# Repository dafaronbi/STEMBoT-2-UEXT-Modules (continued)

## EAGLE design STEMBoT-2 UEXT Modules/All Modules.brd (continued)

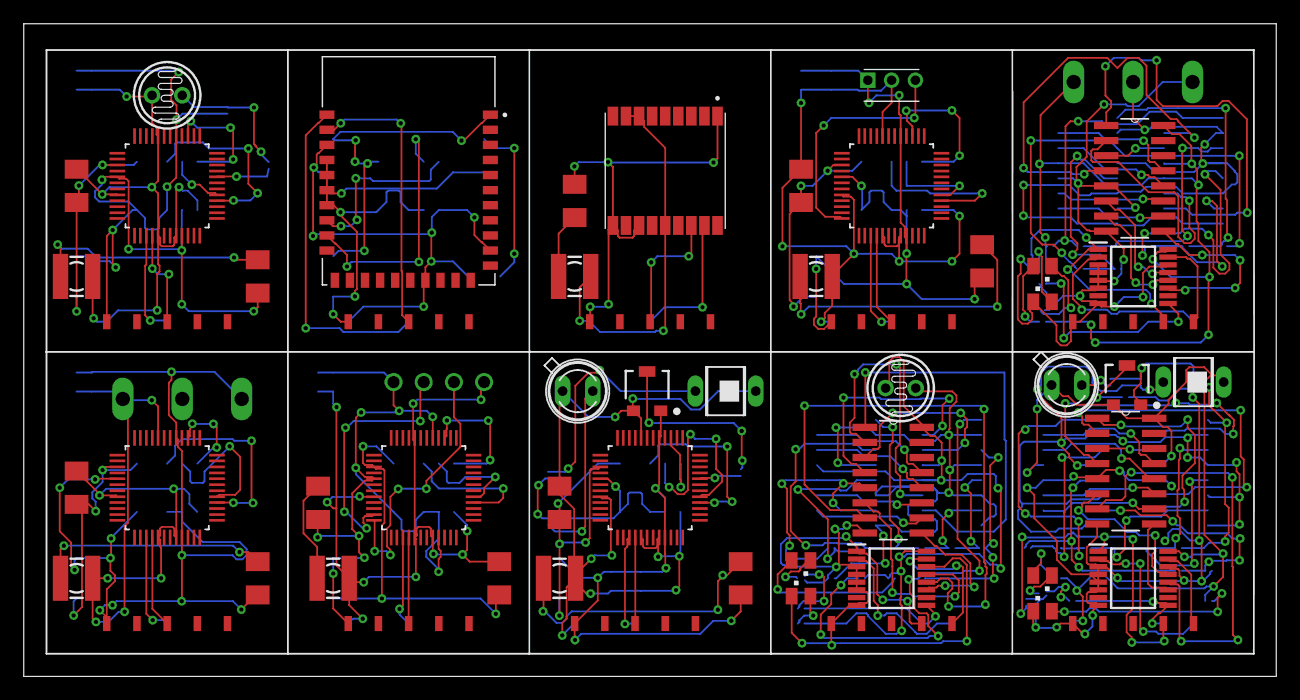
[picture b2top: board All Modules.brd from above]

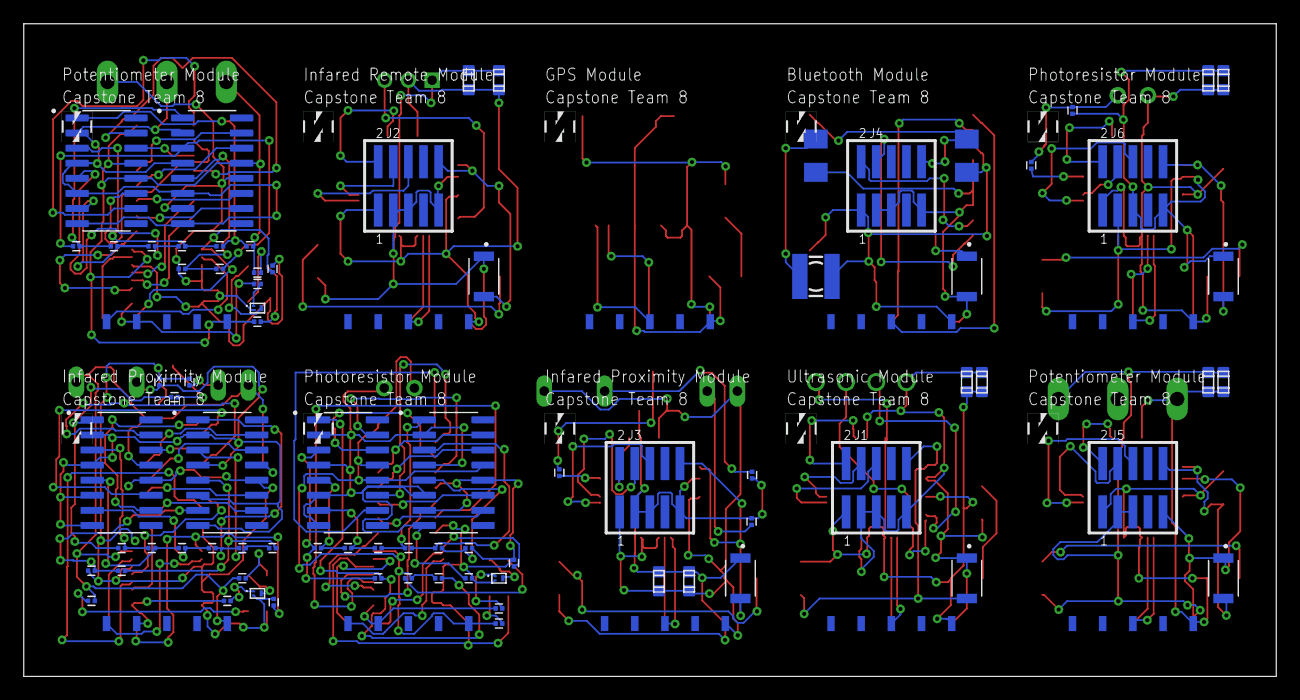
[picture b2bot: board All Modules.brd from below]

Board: 2 copper layers, 105.4 x 54.9 mm, 134 parts (79 on the bottom side), 157 nets.

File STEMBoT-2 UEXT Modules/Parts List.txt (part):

Partlist

Exported from All Modules.sch at 3/26/2020 1:25 PM

EAGLE Version 9.5.1 Copyright (c) 1988-2019 Autodesk, Inc.

Assembly variant: 

Part     Value                Device               Package               Library               Sheet

C1       CAPACITORS-0603      CAPACITORS-0603      C0603                 CAPACITORS            1
C2       CAPACITORS-0603      CAPACITORS-0603      C0603                 CAPACITORS            1
C3       CAPACITORS-0603      CAPACITORS-0603      C0603                 CAPACITORS            1
C4       CAPACITORS-0603      CAPACITORS-0603      C0603                 CAPACITORS            1
C5       CAPACITORS-0603      CAPACITORS-0603      C0603                 CAPACITORS            1
C6       CAPACITORS-0603      CAPACITORS-0603      C0603                 CAPACITORS            1
C7       CAPACITORS-0603      CAPACITORS-0603      C0603                 CAPACITORS            1
C8       CAPACITORS-0603      CAPACITORS-0603      C0603                 CAPACITORS            1
C9       CAPACITORS-0603      CAPACITORS-0603      C0603                 CAPACITORS            1
C10      CAPACITORS-0603      CAPACITORS-0603      C0603                 CAPACITORS            1
D1       SFH482               SFH482               SFH482                led                   1
D2       BP104                BP104                BP104                 opto-trans-siemens    1
D3       SFH482               SFH482               SFH482                led                   1
D4       BP104                BP104                BP104                 opto-trans-siemens    1
IC1      74HC165PW,118        74HC165PW,118        SOP65P640X110-16N     74HC165PW_118         1
IC2      74HC165PW,118        74HC165PW,118        SOP65P640X110-16N     74HC165PW_118         1
IC3      74HC165PW,118        74HC165PW,118        SOP65P640X110-16N     74HC165PW_118         1
J1       FTSH-105-01-XXX-DV-K FTSH-105-01-XXX-DV-K FTSH-105-01-XXX-DV-K  FTSH-105-01-XXX-DV-K  1
J2       FTSH-105-01-XXX-DV-K FTSH-105-01-XXX-DV-K FTSH-105-01-XXX-DV-K  FTSH-105-01-XXX-DV-K  1
J3       FTSH-105-01-XXX-DV-K FTSH-105-01-XXX-DV-K FTSH-105-01-XXX-DV-K  FTSH-105-01-XXX-DV-K  1
J4       FTSH-105-01-XXX-DV-K FTSH-105-01-XXX-DV-K FTSH-105-01-XXX-DV-K  FTSH-105-01-XXX-DV-K  1
J5       FTSH-105-01-XXX-DV-K FTSH-105-01-XXX-DV-K FTSH-105-01-XXX-DV-K  FTSH-105-01-XXX-DV-K  1
J6       FTSH-105-01-XXX-DV-K FTSH-105-01-XXX-DV-K FTSH-105-01-XXX-DV-K  FTSH-105-01-XXX-DV-K  1
LED1     NFSG036BT            NFSG036BT            NFSG036BT             led                   1
LED2     NFSG036BT            NFSG036BT            NFSG036BT             led                   1
LED3     NFSG036BT            NFSG036BT            NFSG036BT             led                   1
LED4     NFSG036BT            NFSG036BT            NFSG036BT             led                   1
LED5     NFSG036BT            NFSG036BT            NFSG036BT             led                   1
LED6     NFSG036BT            NFSG036BT            NFSG036BT             led                   1
LED7     NFSG036BT            NFSG036BT            NFSG036BT             led                   1
LED8     LSG-T676             LSG-T676             P-LCC4-0              led                   1
LED9     LSG-T676             LSG-T676             P-LCC4-0              led                   1
LED10    LSG-T676             LSG-T676             P-LCC4-0              led                   1
PH1      VT20N1               VT20N1               TO46-VT200            photo-elements        1
PH2      VT20N1               VT20N1               TO46-VT200            photo-elements        1
Q1       MMBT3904LP-7         MMBT3904LP-7         DFN101X61X53-3N       NPN BJT               1
Q2       MMBT3904LP-7         MMBT3904LP-7         DFN101X61X53-3N       MMBT3904LP-7          1
Q3       MMBT3904LP-7         MMBT3904LP-7         DFN101X61X53-3N       MMBT3904LP-7          1
R1       ERJ-1RHD3601C        ERJ-1RHD3601C        RESC0603X26N          Resistor              1
R2       ERJ-1RHD3601C        ERJ-1RHD3601C        RESC0603X26N          Resistor              1
R3       ERJ-1RHD3601C        ERJ-1RHD3601C        RESC0603X26N          Resistor              1
R4       ERJ-1RHD3601C        ERJ-1RHD3601C        RESC0603X26N          Resistor              1
R5       ERJ-1RHD3601C        ERJ-1RHD3601C        RESC0603X26N          Resistor              1
R6       1k                   R-EU_M1206           M1206                 rcl                   1
R7       1k                   R-EU_M1206           M1206                 rcl                   1
R8       ERJ-1RHD3601C        ERJ-1RHD3601C        RESC0603X26N          Resistor              1
R9       ERJ-1RHD3601C        ERJ-1RHD3601C        RESC0603X26N          Resistor              1
R10      ERJ-1RHD3601C        ERJ-1RHD3601C        RESC0603X26N          Resistor              1
R11      ERJ-1RHD3601C        ERJ-1RHD3601C        RESC0603X26N          Resistor              1
R12      ERJ-1RHD3601C        ERJ-1RHD3601C        RESC0603X26N          Resistor              1
R13      ERJ-1RHD3601C        ERJ-1RHD3601C        RESC0603X26N          Resistor              1
R15      ERJ-1RHD3601C        ERJ-1RHD3601C        RESC0603X26N          Resistor              1
R16      ERJ-1RHD3601C        ERJ-1RHD3601C        RESC0603X26N          Resistor              1
R17      ERJ-1RHD3601C        ERJ-1RHD3601C        RESC0603X26N          Resistor              1
R18      ERJ-1RHD3601C        ERJ-1RHD3601C        RESC0603X26N          Resistor              1
R19      ERJ-1RHD3601C        ERJ-1RHD3601C        RESC0603X26N          Resistor              1
R20      PC16S(NOSILK)        PC16S(NOSILK)        PC16S(NOSILK)         piher                 1
R21      ERJ-1RHD3601C        ERJ-1RHD3601C        RESC0603X26N          Resistor              1
R22      1k                   R-EU_M1206           M1206                 rcl                   1
R23      ERJ-1RHD3601C        ERJ-1RHD3601C        RESC0603X26N          Resistor              1
R24      ERJ-1RHD3601C        ERJ-1RHD3601C        RESC0603X26N          Resistor              1
R25      ERJ-1RHD3601C        ERJ-1RHD3601C        RESC0603X26N          Resistor              1
R26      ERJ-1RHD3601C        ERJ-1RHD3601C        RESC0603X26N          Resistor              1
R27      ERJ-1RHD3601C        ERJ-1RHD3601C        RESC0603X26N          Resistor              1
R28      ERJ-1RHD3601C        ERJ-1RHD3601C        RESC0603X26N          Resistor              1
R29      ERJ-1RHD3601C        ERJ-1RHD3601C        RESC0603X26N          Resistor              1
R30      ERJ-1RHD3601C        ERJ-1RHD3601C        RESC0603X26N          Resistor              1
R31      ERJ-1RHD3601C        ERJ-1RHD3601C        RESC0603X26N          Resistor              1
R32      ERJ-1RHD3601C        ERJ-1RHD3601C        RESC0603X26N          Resistor              1
R33      ERJ-1RHD3601C        ERJ-1RHD3601C        RESC0603X26N          Resistor              1
R34      ERJ-1RHD3601C        ERJ-1RHD3601C        RESC0603X26N          Resistor              1
R35      ERJ-1RHD3601C        ERJ-1RHD3601C        RESC0603X26N          Resistor              1
R36      ERJ-1RHD3601C        ERJ-1RHD3601C        RESC0603X26N          Resistor              1
R37      ERJ-1RHD3601C        ERJ-1RHD3601C        RESC0603X26N          Resistor              1
R38      ERJ-1RHD3601C        ERJ-1RHD3601C        RESC0603X26N          Resistor              1
R39      ERJ-1RHD3601C        ERJ-1RHD3601C        RESC0603X26N          Resistor              1
R40      ERJ-1RHD3601C        ERJ-1RHD3601C        RESC0603X26N          Resistor              1
R41      ERJ-1RHD3601C        ERJ-1RHD3601C        RESC0603X26N          Resistor              1
R42      ERJ-1RHD3601C        ERJ-1RHD3601C        RESC0603X26N          Resistor              1
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
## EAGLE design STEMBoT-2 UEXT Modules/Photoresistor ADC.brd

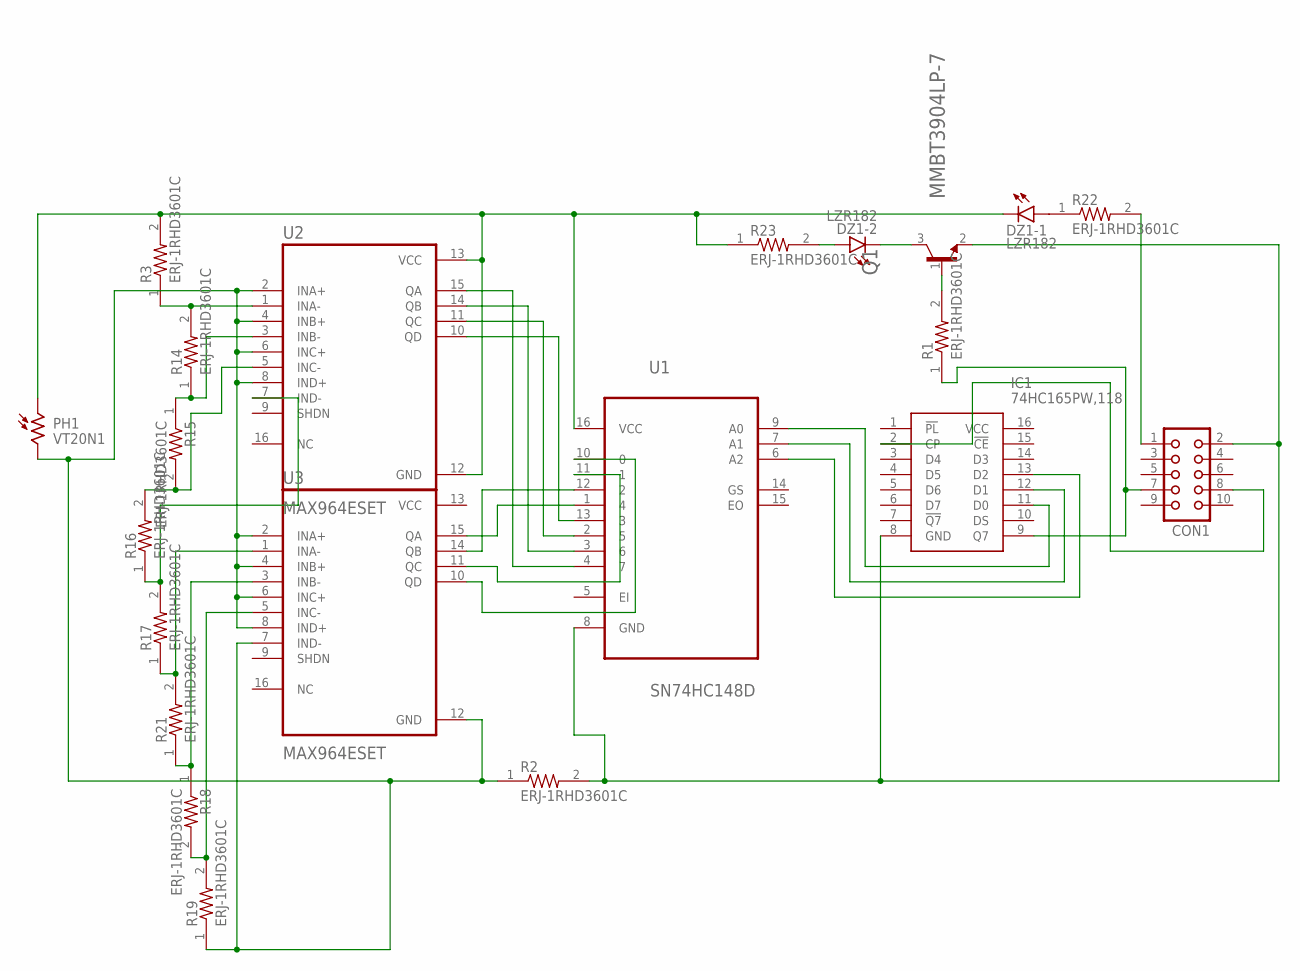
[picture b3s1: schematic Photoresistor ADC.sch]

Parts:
CON1: CON10L
DZ1: LZR182
IC1: 74HC165PW,118; SOP65P640X110-16N
PH1: VT20N1; TO46-VT200
Q1: MMBT3904LP-7; DFN101X61X53-3N
R1, R2, R3, R14, R15, R16, R17, R18, R19, R21, R22, R23: ERJ-1RHD3601C; RESC0603X26N
U1: SN74HC148D; SOIC127P600X175-16N
U2, U3: MAX964ESET; SOIC127P600X175-16N

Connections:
unnamed: Q1.1 (B), R1.2
unnamed: R15.2, R16.2, U2.5 (INC-)
unnamed: DZ1.A1 (A), R22.1
unnamed: DZ1.K2 (C), Q1.3 (C)
unnamed: CON1.1, R22.2
unnamed: CON1.7, IC1.9 (Q7), R1.1
unnamed: R3.1, R14.2, U2.1 (INA-)
unnamed: R14.1, R15.1, U2.3 (INB-)
unnamed: R16.1, R17.2, U2.7 (IND-)
unnamed: R17.1, R21.2, U3.1 (INA-)
unnamed: DZ1.K1 (C), PH1.1, R3.2, R23.1, U1.16 (VCC), U2.12 (GND), U2.13 (VCC)
unnamed: R18.1, R21.1, U3.3 (INB-)
unnamed: R18.2, R19.2, U3.5 (INC-)
unnamed: PH1.2, R2.1, R19.1, U2.2 (INA+), U2.4 (INB+), U2.6 (INC+), U2.8 (IND+), U3.2 (INA+), U3.4 (INB+), U3.6 (INC+), U3.7 (IND-), U3.8 (IND+), U3.12 (GND)
unnamed: U1.4 (7), U2.15 (QA)
unnamed: U1.3 (6), U2.14 (QB)
unnamed: U1.2 (5), U2.11 (QC)
unnamed: IC1.11 (D0), U1.9 (A0)
unnamed: IC1.12 (D1), U1.7 (A1)
unnamed: IC1.13 (D2), U1.6 (A2)
unnamed: CON1.2, IC1.8 (GND), Q1.2 (E), R2.2, U1.8 (GND)
unnamed: U1.13 (3), U2.10 (QD)
unnamed: CON1.8, IC1.2 (CP)
unnamed: DZ1.A2 (A), R23.2
unnamed: U1.1 (4), U3.15 (QA)
unnamed: U1.12 (2), U3.14 (QB)
unnamed: U1.11 (1), U3.11 (QC)
unnamed: U1.10 (0), U3.10 (QD)
VCC: U3.13 (VCC)

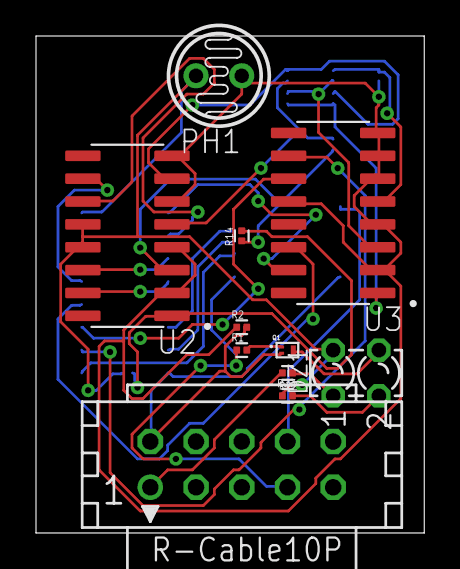
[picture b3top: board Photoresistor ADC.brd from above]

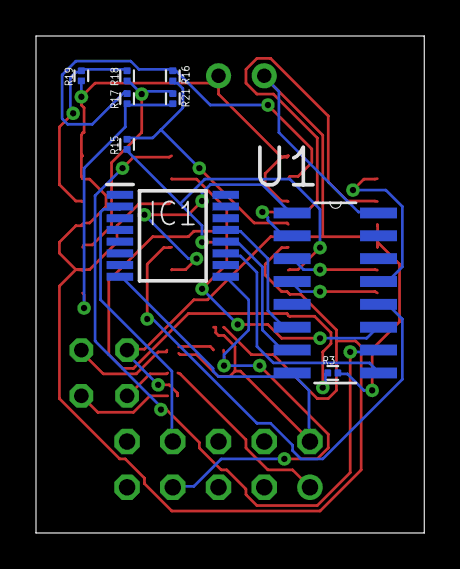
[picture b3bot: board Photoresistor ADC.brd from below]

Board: 2 copper layers, 21.6 x 27.6 mm, 20 parts (9 on the bottom side), 28 nets.

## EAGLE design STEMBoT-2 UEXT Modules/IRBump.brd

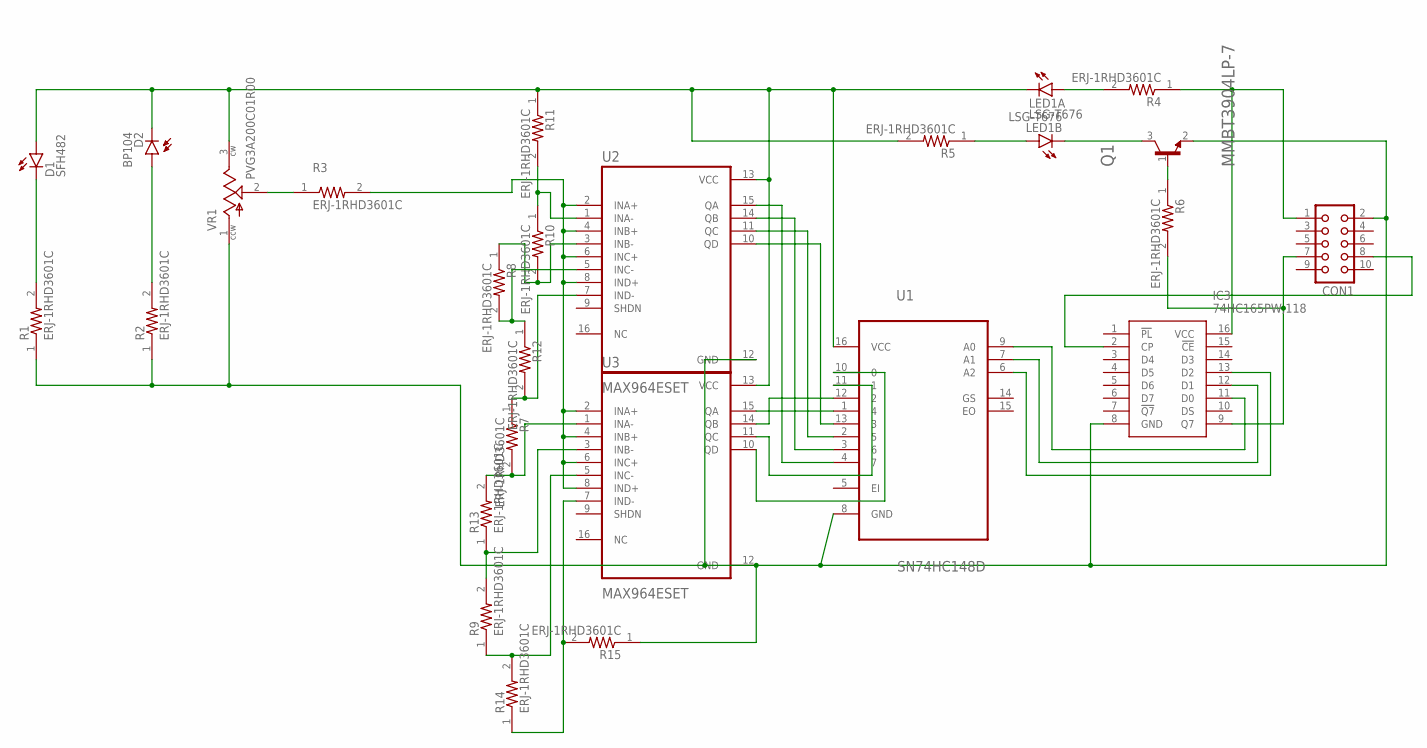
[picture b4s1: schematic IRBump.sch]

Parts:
CON1: CON10
D1: SFH482
D2: BP104
IC3: 74HC165PW,118; SOP65P640X110-16N
LED1: LSG-T676; P-LCC4-0
Q1: MMBT3904LP-7; DFN101X61X53-3N
R1, R2, R3, R4, R5, R6, R7, R8, R9, R10, R11, R12, R13, R14, R15: ERJ-1RHD3601C; RESC0603X26N
U1: SN74HC148D; SOIC127P600X175-16N
U2, U3: MAX964ESET; SOIC127P600X175-16N
VR1: PVG3A200C01R00; TRIM_PVG3A200C01R00

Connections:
unnamed: R3.2, U2.2 (INA+), U2.4 (INB+), U2.6 (INC+), U2.8 (IND+), U3.2 (INA+), U3.4 (INB+), U3.6 (INC+), U3.8 (IND+)
unnamed: D1.K (C), R1.2
unnamed: LED1.4 (A), R5.1
unnamed: CON1.2, IC3.8 (GND), Q1.2 (E), R1.1, R2.1, R15.1, U1.8 (GND), U2.12 (GND), U3.12 (GND), VR1.1 (CCW)
unnamed: U1.4 (7), U2.15 (QA)
unnamed: D1.A, D2.K (C), LED1.1 (C), R5.2, R11.1, U1.16 (VCC), U2.13 (VCC), U3.13 (VCC), VR1.3 (CW)
unnamed: D2.A, R2.2
unnamed: LED1.3 (C), Q1.3 (C)
unnamed: R10.1, R11.2, U2.1 (INA-)
unnamed: LED1.2 (A), R4.2
unnamed: R8.1, R10.2, U2.3 (INB-)
unnamed: Q1.1 (B), R6.1
unnamed: R8.2, R12.1, U2.5 (INC-)
unnamed: R3.1, VR1.2 (WIPER)
unnamed: R7.1, R12.2, U2.7 (IND-)
unnamed: R7.2, R13.2, U3.1 (INA-)
unnamed: CON1.1, IC3.16 (VCC), R4.1
unnamed: R9.2, R13.1, U3.3 (INB-)
unnamed: R9.1, R14.2, U3.5 (INC-)
unnamed: R14.1, R15.2, U3.7 (IND-)
unnamed: U1.3 (6), U2.14 (QB)
unnamed: U1.2 (5), U2.11 (QC)
unnamed: U1.13 (3), U2.10 (QD)
unnamed: U1.1 (4), U3.15 (QA)
unnamed: CON1.8, IC3.2 (CP)
unnamed: U1.12 (2), U3.14 (QB)
unnamed: IC3.11 (D0), U1.9 (A0)
unnamed: IC3.12 (D1), U1.7 (A1)
unnamed: IC3.13 (D2), U1.6 (A2)
unnamed: CON1.7, IC3.9 (Q7), R6.2
unnamed: U1.11 (1), U3.11 (QC)
unnamed: U1.10 (0), U3.10 (QD)

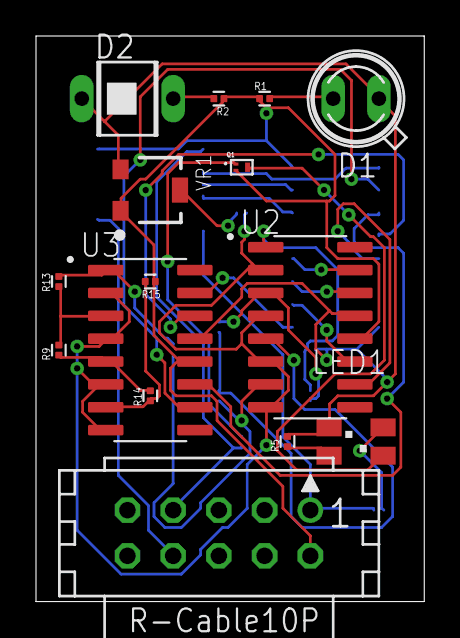
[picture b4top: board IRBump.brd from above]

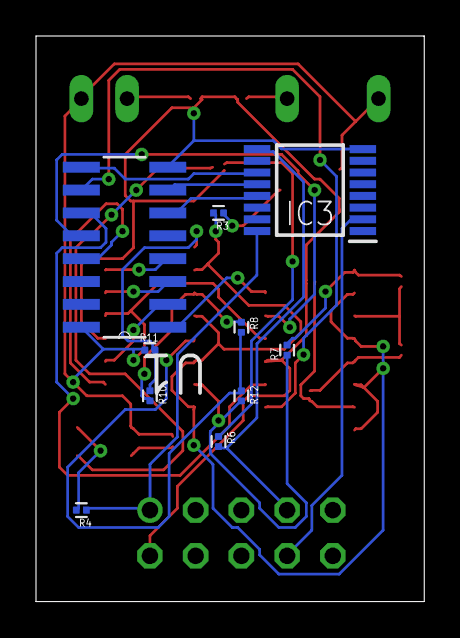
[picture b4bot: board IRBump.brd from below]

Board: 2 copper layers, 21.6 x 31.4 mm, 25 parts (10 on the bottom side), 32 nets.

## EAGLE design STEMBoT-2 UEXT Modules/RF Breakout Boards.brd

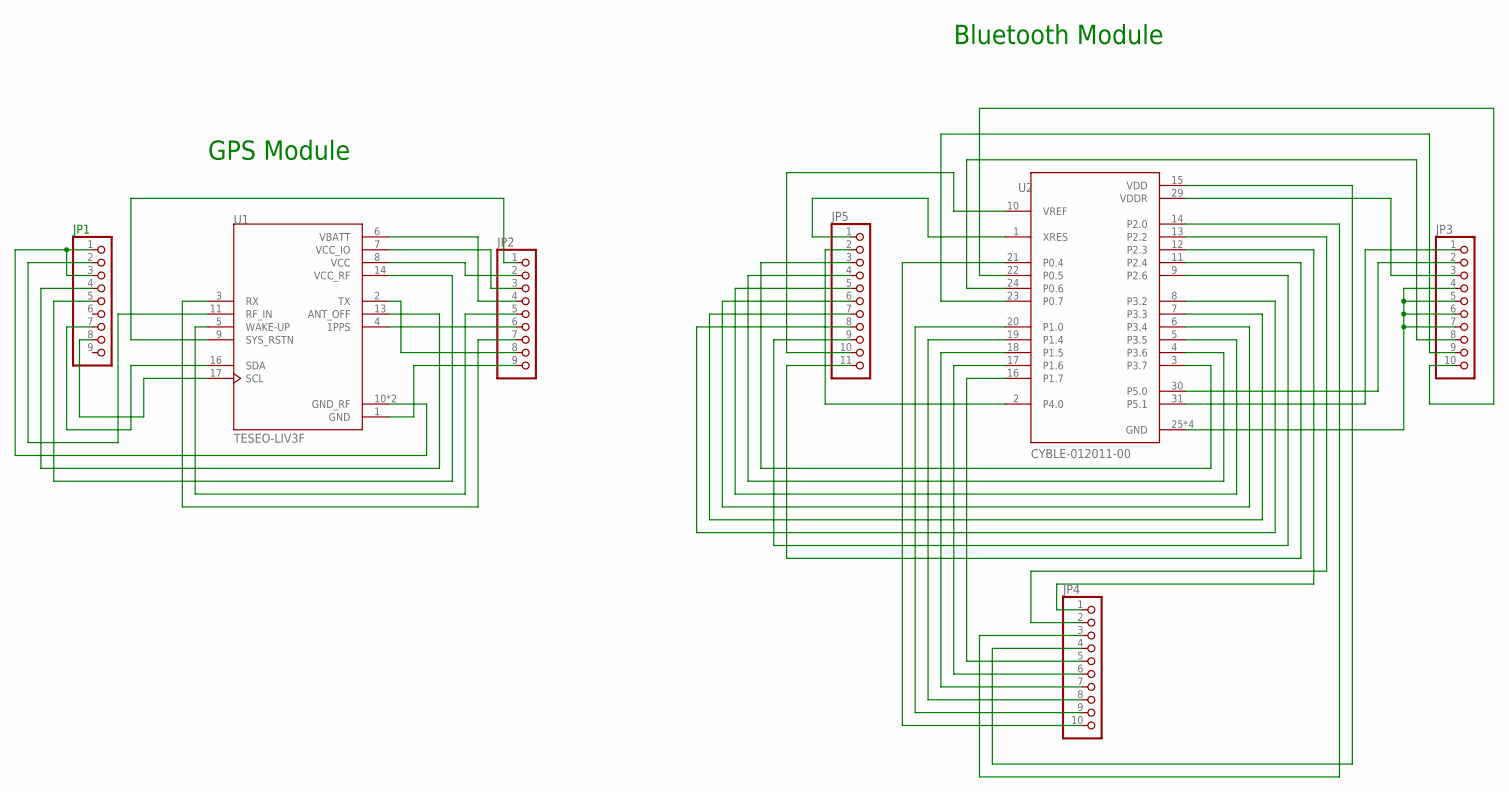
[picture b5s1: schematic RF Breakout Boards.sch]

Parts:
JP1, JP2: PINHD-1X9; 1X09
JP3, JP4: PINHD-1X10; 1X10
JP5: PINHD-1X11; 1X11
U1: TESEO-LIV3F
U2: CYBLE-012011-00; XCVR_CYBLE-012011-00

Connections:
1PPS: JP2.6, U1.4 (1PPS)
ANT_OFF: JP1.4, U1.13 (ANT_OFF)
GND: JP2.9, U1.1 (GND)
GND2: JP3.4, JP3.5, JP3.6, JP3.7, U2.25 (GND), U2.26 (GND), U2.27 (GND), U2.28 (GND)
GND_RF: JP1.1, JP1.3, U1.10 (GND_RF), U1.12 (GND_RF)
P0.4: JP4.10, U2.21 (P0.4)
P0.5: JP3.10, U2.22 (P0.5)
P0.6: JP3.8, U2.24 (P0.6)
P0.7: JP3.9, U2.23 (P0.7)
P1.0: JP4.9, U2.20 (P1.0)
P1.4: JP4.8, U2.19 (P1.4)
P1.5: JP4.7, U2.18 (P1.5)
P1.6: JP4.6, U2.17 (P1.6)
P1.7: JP4.5, U2.16 (P1.7)
P2.0: JP4.3, U2.14 (P2.0)
P2.2: JP4.2, U2.13 (P2.2)
P2.3: JP4.1, U2.12 (P2.3)
P2.4: JP5.11, U2.11 (P2.4)
P2.6: JP5.9, U2.9 (P2.6)
P3.2: JP5.8, U2.8 (P3.2)
P3.3: JP5.7, U2.7 (P3.3)
P3.4: JP5.6, U2.6 (P3.4)
P3.5: JP5.5, U2.5 (P3.5)
P3.6: JP5.4, U2.4 (P3.6)
P3.7: JP5.3, U2.3 (P3.7)
P4.0: JP5.2, U2.2 (P4.0)
P5.0: JP3.2, U2.30 (P5.0)
P5.1: JP3.1, U2.31 (P5.1)
RF_IN: JP1.2, U1.11 (RF_IN)
RX: JP2.7, U1.3 (RX)
SCL: JP1.8, U1.17 (SCL)
SDA: JP1.7, U1.16 (SDA)
SYS_RSTN: JP2.1, U1.9 (SYS_RSTN)
TX: JP2.8, U1.2 (TX)
VBATT: JP2.4, U1.6 (VBATT)
VCC: JP2.2, U1.8 (VCC)
VCC_IO: JP2.3, U1.7 (VCC_IO)
VCC_RF: JP1.5, U1.14 (VCC_RF)
VDD: JP4.4, U2.15 (VDD)
VDDR: JP3.3, U2.29 (VDDR)
VREF: JP5.10, U2.10 (VREF)
WAKE-UP: JP2.5, U1.5 (WAKE-UP)
XRES: JP5.1, U2.1 (XRES)

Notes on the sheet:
GPS Module
Bluetooth Module

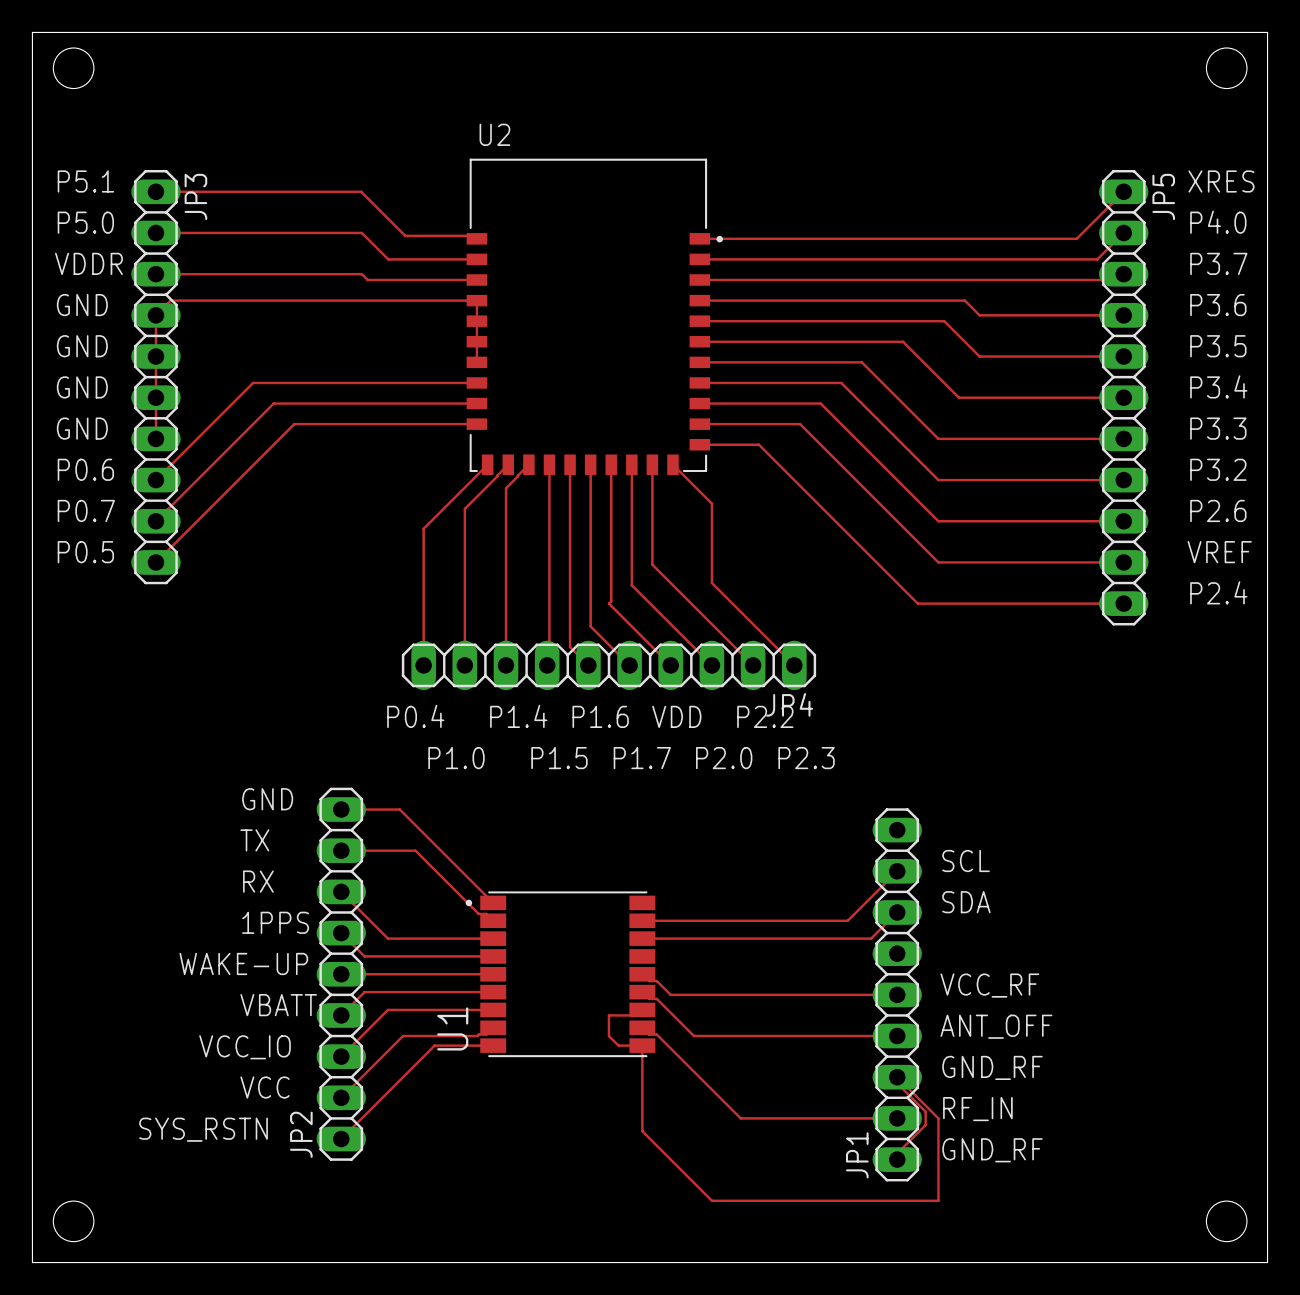
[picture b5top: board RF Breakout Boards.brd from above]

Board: 2 copper layers, 76.2 x 75.9 mm, 7 parts (0 on the bottom side), 43 nets.

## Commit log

2020-02-10 New folders
2020-02-11 added new folders and eagle project
2020-02-11 added board, schematic, and gerber files for rf breakout board
2020-02-12 added schematic for gps and bluetooth modules
2020-02-12 Create ADC schem.s#1
2020-02-12 Create Photoresistor schem.s#1
2020-02-14 added software for lpc11C24
2020-02-14 added test program for lpc11C24
2020-02-17 added new file to test branching
2020-02-17 deleted useless test file
2020-02-17 updated readme with project proposal
2020-02-17 added useless file
2020-02-17 deleted useless file
2020-02-23 added footprints for microcontroller and uext connector
2020-02-24 added schematic and board for all modules
2020-02-27 changes to pcb with 6 mil traces
2020-02-29 Testing and experimenting with github commits and branches
2020-02-29 added files lpc4088 proggraming to test bluetooth module
2020-02-29 Revert "added files lpc4088 proggraming to test bluetootth module"
    This reverts commit 1ce47f8c1a4cb860fc41099bd697838798199396.
2020-02-29 added files lpc4088 proggraming to test bluetootth module
2020-02-29 added update files
2020-02-29 Revert "Revert "added files lpc4088 proggraming to test bluetootth module""
    This reverts commit 1a1449da974461db6e68311b52b2f85fcb3c5801.
2020-02-29 added random:
2020-02-29 added source files for test program
2020-02-29 deleted useless files
2020-02-29 added i2c send
2020-02-29 added system tick file
2020-02-29 added delay and startup blink
2020-02-29 added i2c example file
2020-02-29 got i2c pins to have master output with dan's old program that was modified for this board
2020-03-06 added psoc test project and keil uvision project
2020-03-09 Added board and schematic file for new IR sensor design
2020-03-09 Added Photoresistor and Potentiometer to ADC design
2020-03-09 Removed old ADC schematic and breadboard designs
2020-03-10 working program for interfacing bluetooth module with phone
2020-03-13 Adjusted ADC modules for PCB order. Dan, these are auto-routed.
2020-03-14 Once again, updating ADC shematics and boards. Used autorouter.
2020-03-16 The new design for ADC modules.
2020-03-16 Component footprints for ADC design.
2020-03-16 added library for jtag header
2020-03-17 added changes to adc shematic design
2020-03-17 improved schematics
2020-03-17 added workspace
2020-03-17 workspace now working
2020-03-18 added test adc program
2020-03-18 added tactile switch library fil
2020-03-18 added libraries for ir and ultrasonic
2020-03-18 finished schematic
2020-03-18 added new schematic changes
2020-03-18 added board file and new switch library
2020-03-18 removed silk screens
2020-03-18 update pot library
2020-03-19 Added random test file
2020-03-19 changes to board and schematic
2020-03-19 added project for adc spi test
2020-03-19 working code for spi read
2020-03-19 update led footprint
2020-03-19 added project for spi test
2020-03-20 final spi test program
2020-03-20 final software for adc test
2020-03-20 final pcb traces
2020-03-20 finish pcb traces
2020-03-22 final pcb board layout for reveiw
2020-03-23 I am a little wary off all this stuff in here. I went ahead and added an ultrasonic schem in here. Dont know why it wasnt in before.
2020-03-23 final board design and generated gerber files
2020-03-25 add first board program
2020-03-25 added initial custo bluetooth program
2020-03-25 Revert "working program for interfacing bluetooth module with phone"
    This reverts commit c2fadbbac45497b8c3b2bf5b94f375256a6d6b6d.
2020-03-25 added custom bluetooth program initial project
2020-03-26 code for working bluetooth with battery
2020-03-26 added parts list
2020-03-27 added LPC4088 space
2020-03-27 updated workspace with new code
2020-03-27 added i2c read test app
2020-03-27 working batter level code
2020-03-28 added saved stembot-2 firmware
2020-03-29 added test applications for STEMBoT-2
2020-03-30 added new scripts
2020-04-03 added i2c test program
2020-04-03 added bluetooth i2c test from lpc4088
2020-04-04 final working firmware for bluetoothhh complete
2020-04-14 uext connector modified
2020-05-14 added inductor footprint
2020-05-14 added new gps schematic and board
2020-05-14 added gps gerber files
2020-05-17 Current Firmware for IR-Remote-Control device
2020-08-06 more clean readme
2020-08-06 changed formatting
